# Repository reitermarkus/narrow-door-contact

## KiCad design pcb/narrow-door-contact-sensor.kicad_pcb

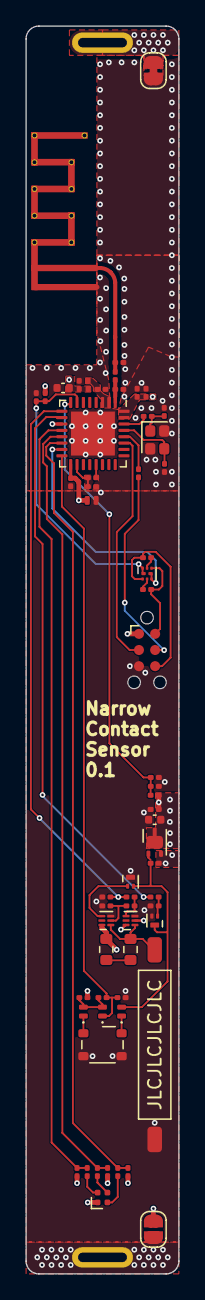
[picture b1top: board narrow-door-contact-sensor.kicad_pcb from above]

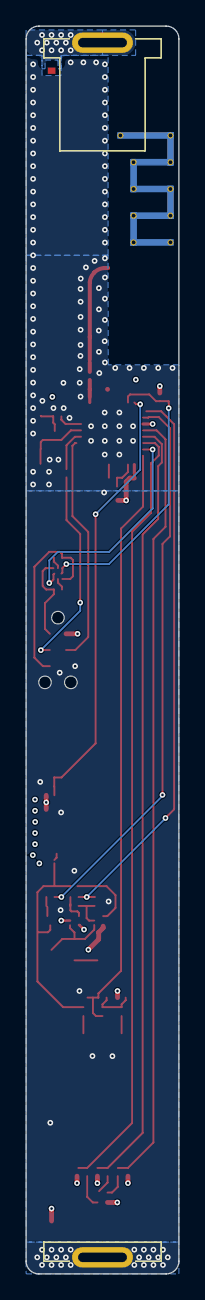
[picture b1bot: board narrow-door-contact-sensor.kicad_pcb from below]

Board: 4 copper layers, 12.0 x 98.0 mm, 64 parts (2 on the bottom side), 41 nets.

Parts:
AE1: Inverted_F_Antenna_2.4GHz_Meandered; ESP32-C3-MINI-1_Inverted_F_Antenna
C1, C2: 10pF; C_0201_0603Metric
C3, C11, C16, C17: 1uF; C_0201_0603Metric
C4, C12: 10nF; C_0201_0603Metric
C5, C15: 10uF; C_0402_1005Metric
C6, C7, C10, C13: 0.1uF; C_0201_0603Metric
C8, C9: 3pF; C_0201_0603Metric
C14: 4.7uF; C_0201_0603Metric
CN1: 5226; Keystone_5226
CN2: 5204; Keystone_5204
D1: ESD9B3.3ST5G; DFN1006-2L-BI
D2: NH-B1010RGBT-HF; LED-ARRAY-SMD_4P-L1.0-W1.0-TR_NH-B1010RGBT
D3, D4, D5: 1.1V; SOD-882_L1.0-W0.6-RD
JP1: SolderJumper_2_Bridged; SolderJumper-2_P1.3mm_Open_RoundedPad1.0x1.5mm
JP2: SolderJumper_2_Bridged; SolderJumper-2_P1.3mm_Bridged_RoundedPad1.0x1.5mm
L1, L2: 2nH; L_0201_0603Metric
P1: TC2030-NL; Tag-Connect_TC2030-IDC-NL_2x03_P1.27mm_Vertical
Q1: DMN2005LP4K-7; X2-DFN1006-3_L1.0-W0.6-P0.35-BL
Q2: BC847QASZ; DFN1010B-6_L1.1-W1.0-P0.35-BL
Q3: BC857BMB,315; X2-DFN1006-3_L1.0-W0.6-BR
Q4: DMG3415UFY4Q-7; X2-DFN2015-3_L2.0-W1.5-P0.50-BR
R1: 0Ω; R_0201_0603Metric
R2: 499Ω; R_0201_0603Metric
R3, R18, R19: 100kΩ; R_0201_0603Metric
R4: 150kΩ; R_0201_0603Metric
R5, R8, R13, R20, R23, R24: 10kΩ; R_0201_0603Metric
R6, R7, R9, R21: 45kΩ; R_0201_0603Metric
R10: 510Ω; R_0201_0603Metric
R11, R12: 680Ω; R_0201_0603Metric
R14, R17: 1MΩ; R_0201_0603Metric
R15, R16: 100MΩ; R_0603_1608Metric
R22: 1kΩ; R_0201_0603Metric
SW1: 59170-1-S-00-D; SENSOR-SMD_59170-1-S-00-D
SW2: SW_Push; SW-SMD_4P-L3.0-W2.6-P1.80-LS3.4-TL
U1: ESP32-C3FH4; QFN-32-1EP_5x5mm_P0.5mm_EP3.45x3.45mm
U2, U3: 74AUP1G86FW4-7; X2-DFN1010-6_L1.0-W1.0-P0.35-BL
Y1: 40MHz; CRYSTAL-SMD_4P-L2.0-W1.6-BL

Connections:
+3.3V: C3.1, C4.1, C5.2, C6.1, C10.2, C15.2, C16.2, D1.2 (A2), D2.1 (A), JP1.1 (A), L1.1, P1.1 (VCC), Q4.3 (D), R3.2, R5.2, R6.1, R7.1, R9.1, R21.2, U1.11 (VDD3P3_RTC), U1.17 (VDD3P3_CPU), U1.31 (VDDA), U1.32 (VDDA)
+BATT: CN1.1 (+), JP1.2 (B), Q4.2 (S), R15.2, R17.1, U2.2, U2.6 (VCC), U3.6 (VCC)
-BATT: CN2.1 (-), JP2.2 (B)
/ADC1_CH3: C12.1, R3.1, R4.1, U1.8 (GPIO3/ADC1_CH3)
/CHIP_EN: C13.1, Q2.6 (C1), Q2.7 (C1), R5.1, U1.7 (CHIP_EN)
/Configuration Button/BTN_A: D4.2 (A), D5.2 (A), R21.1, R22.1
/Configuration Button/BTN_K: D4.1 (K), SW2.1
/GPIO4: R13.2, R14.1, U1.9 (MTMS/GPIO4/ADC1_CH4)
/GPIO5: R20.2, U1.10 (MTDI/GPIO5/ADC2_CH0)
/GPIO6: R6.2, R10.2, U1.12 (MTCK/GPIO6)
/GPIO7: R7.2, R11.2, U1.13 (MTDO/GPIO7)
/GPIO8: R9.2, R12.2, U1.14 (GPIO8)
/GPIO9: Q2.3 (C2), Q2.8 (C2), U1.15 (GPIO9/BOOT)
/GPIO10: C17.1, D5.1 (K), R22.2, U1.16 (GPIO10)
/LED_B: D2.4 (BK), R12.1
/LED_G: D2.3 (GK), R11.1
/LED_R: D2.2 (RK), R10.1
/LNA_IN: C9.1, L2.2, U1.1 (LNA_IN)
/POWER_ON: D3.1 (K), SW2.2
/Power Latch/AUTO_POWER: Q3.1 (B), U3.4
/Power Latch/DELAY_IN: R13.1, R18.1, U2.4
/Power Latch/DELAY_OUT: C14.1, R18.2, U3.2
/Power Latch/SW1: R16.2, SW1.2, U2.1, U3.1
/Programming Connection/DTR: P1.2 (DTR), Q2.4 (E2), R23.1
/Programming Connection/DTR_B: Q2.2 (B1), R23.2
/Programming Connection/RTS: P1.6 (RTS), Q2.1 (E1), R24.1
/Programming Connection/RTS_B: Q2.5 (B2), R24.2
/RF_ANT: AE1.1 (A), C8.1, L2.1
/SPICS0: R8.2, U1.21 (SPICS0/GPIO14)
/U0RXD: P1.3 (RXD), U1.27 (U0RXD/GPIO20)
/U0TXD: R2.1, U1.28 (U0TXD/GPIO21)
/U0TXD_R: P1.4 (TXD), R2.2
/VDD3P3: C7.1, L1.2, U1.2 (VDD3P3), U1.3 (VDD3P3)
/VDD_SPI: C11.2, R8.1, U1.18 (VDD_SPI/GPIO11)
/XTAL_N: C2.1, U1.29 (XTAL_N), Y1.3
/XTAL_P: R1.1, U1.30 (XTAL_P)
/XTAL_P_R: C1.1, R1.2, Y1.1
GND: AE1.2 (GND), C1.2, C2.2, C3.2, C4.2, C5.1, C6.2, C7.2, C8.2, C9.2, C10.1, C11.1, C12.2, C13.2, C14.2, C15.1, C16.1, C17.2, D1.1 (A1), JP2.1 (A), P1.5 (GND), Q1.2 (S), Q3.3 (C), R4.2, R14.2, R19.2, SW1.1, SW2.3, SW2.4, U1.33 (GND), U2.3 (GND), U3.3 (GND), Y1.2, Y1.4
unnamed: D3.2 (A), Q1.3 (D), Q3.2 (E), Q4.1 (G), R17.2
unnamed: Q1.1 (G), R19.1, R20.1
unnamed: R15.1, R16.1

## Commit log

2023-12-26 Add PCB.
